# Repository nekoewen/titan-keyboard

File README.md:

# The Titan
The Titan is a QMK-powered keyboard for playing video games, particularly but not exclusively fighting games. The design mixes in bits of the Sega Saturn controller (hence I named it after one of Saturn’s moons) and Hitbox controllers.

## Bill of Materials
- Pro Micro (or a compatible microcontroller, such as an Elite-C, BIT-C, KB2040, etc.) with headers
- 17x 1N4148 through-hole diodes
- 17x key switches (MX or Choc)
- 17x keycaps; 15 should be 1u, and two should be 1.5u
- 9x M2 standoffs
- 18x M2 screws
- 4 or more adhesive rubber feet
- 2-pin reset switch (optional; 3x6x2mm DIP-2P switch, the same kind used on the Corne keyboard)
- EC11 encoder switch with knob (optional)
- WS2182B LED strip and 3 wires (optional)

## Tools
- Soldering iron with solder
- Wire clippers
- Wire stripper (if including an LED strip)
- Screwdriver
- Diode bending tool (optional; I use [this one](https://www.thingiverse.com/thing:4332520))

## Build Guide
1. Begin with the diodes. Bend the leads, insert them through the holes (the cathode is marked with a black line and should go on the square pad, so that the line on the diode matches the one printed on the PCB). Solder each diode, then use clippers to remove the excess leads.
2. Take your Pro Micro and flash the firmware (see below). I recommend doing this before soldering it just in case you got a bad board.
3. Solder the Pro Micro and its header pins to the underside of the board, with the Pro Micro’s components facing the board. You may want to use your clippers to trim off the excess part of the headers. If you’re adding a reset switch, put it into the PCB and solder its pins.
4. If you’re going to use an EC11 encoder, solder it in place now. If you wait until you've soldered the switches, the top plate will being in the way will make it incredibly difficult to get the EC11 in place.
5. From here you should be able to test the keyboard’s functionality. If you plug it in, it should register as a Titan keyboard, and you can use tweezers or a similar metal object to make contact on the switch pads to create the equivalent of keystrokes. If any of the keys don’t work, check to make sure you have the diodes soldered and facing the right direction, and also that the Pro Micro’s pins are all soldered in.
6. Use screws to attach the standoffs to the top plate. It's a bit easier to do this step now.
7. Put the top plate in place, and start pushing switches in place, though the plate and into the PCB so that each switch’s two leads go through the corresponding holes in the PCB. I like to put switches in the corners, solder them in place, and then fill in the rest of the switches. Once you’ve soldered all of the switches, I recommend testing the keyboard again to be sure that you have in fact soldered all of them. Once that’s done you can go ahead and put on the keycaps.
8. If you’re including an LED strip for pretty lights, use 3 wires to solder the pads on the PCB to the corresponding ones on the strip. Be sure the DIn lead is going to LED DAT on the board, as they won’t work if you attach it to DOut on the LED strip. If you plug it into your computer now, it should light up!
9. Flip the keyboard over, put the bottom plate in place (the placement of the screws make it so you need to orient it correctly), and use more screws to secure it in place.
10. Finally, put some adhesive rubber feet on the bottom. You’re done!

## Firmware
You can find a .hex file of the default Titan firmware in this repository. If you don’t have any need to customize the layout, you can just download this and flash it to your Pro Micro.
1. Install [QMK Toolbox](https://github.com/qmk/qmk_toolbox) if you haven’t already.
2. Open titan_default.hex.
3. Click the “Auto-Flash” checkbox.
4. Plug the Pro Micro into your computer.
5. Bridge the GND and RST pins with a metal object (or if it’s already soldered in place, press the reset switch).
6. QMK Toolbox should automatically flash the firmware for you!

If you want to customize the firmware:
1. Copy the “titan” folder from the firmware folder here into the “keyboards” folder of your [QMK installation](https://docs.qmk.fm/#/newbs_getting_started). You can modify the files in this folder as desired.
2. Open a terminal window (for your OS if you’re using macOS or Linux, or [QMK MSYS](https://msys.qmk.fm/) if you’re using Windows).
3. Navigate to the QMK folder (typically `cd qmk_firmware`).
4. Type “`make titan:default`” (or replace “default” with the name of your new keymap) and it should compile.
5. Type “`make titan:default:flash`" (or replace flash with “`dfu`”) to flash it.

If you're using a KB2040 or similar controller, you'll need to use QMK's [Converters](https://github.com/qmk/qmk_firmware/blob/4020674163fc80914059c4c9c3be5c0ae00bd150/docs/feature_converters.md) feature, so for example compiling and flashing for a KB2040 would go as follows:

`qmk flash -c -kb titan -km default -e CONVERT_TO=kb2040`

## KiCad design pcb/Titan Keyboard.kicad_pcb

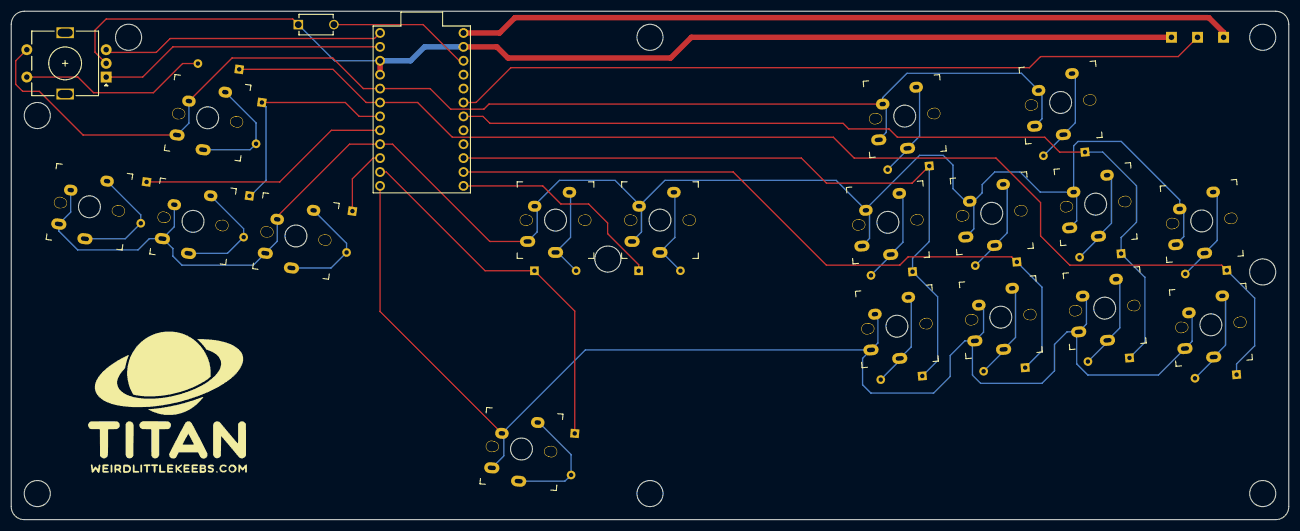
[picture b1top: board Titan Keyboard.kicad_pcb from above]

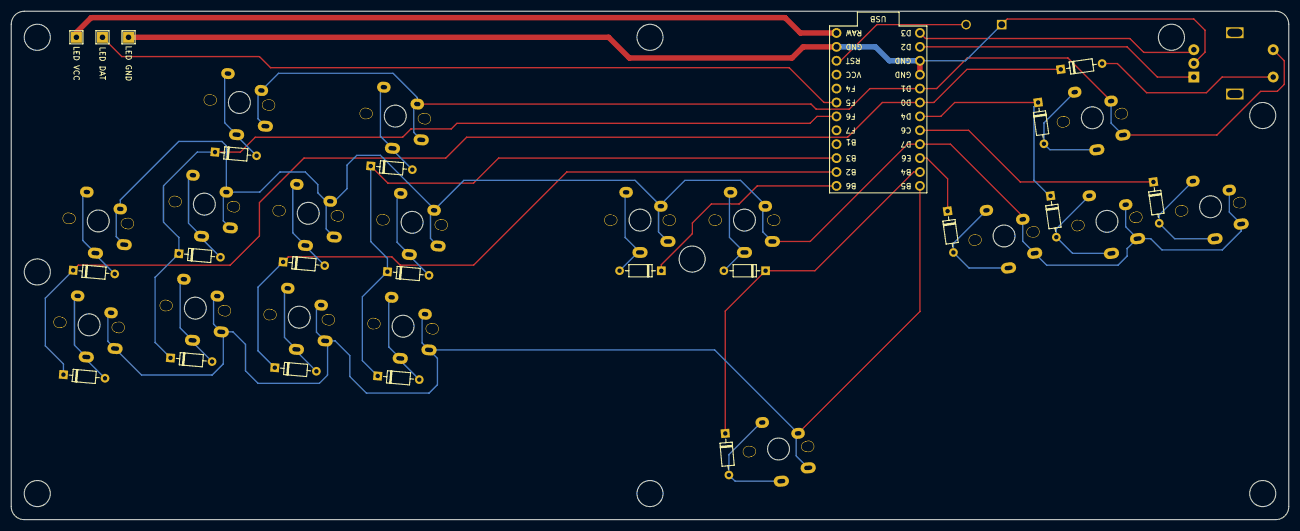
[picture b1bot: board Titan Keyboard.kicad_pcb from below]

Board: 2 copper layers, 233.4 x 92.9 mm, 41 parts (21 on the bottom side), 36 nets.

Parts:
D1, D2, D3, D7, D11, D16, D17, D20, D24, D25, D26, D29, D30, D32, D33, D34, D37, D38: D; D_DO-35_SOD27_P7.62mm_Horizontal
J1: LED VCC; TestPoint_THTPad_2.0x2.0mm_Drill1.0mm
J2: LED DAT; TestPoint_THTPad_2.0x2.0mm_Drill1.0mm
J3: LED GND; TestPoint_THTPad_2.0x2.0mm_Drill1.0mm
SW1: RESET; 1825965-1
SW2: LEFT; CherryMX_Choc_1u
SW3: UP; CherryMX_Choc_1u
SW4: RotaryEncoder_Switch; RotaryEncoder_Alps_EC11E-Switch_Vertical_H20mm
SW8: DWN; CherryMX_Choc_1u
SW12: RIGHT; CherryMX_Choc_1u
SW17: ESC; CherryMX_Choc_1u
SW18: JUMP; CherryMX_Choc_1u
SW21: ENT; CherryMX_Choc_1u
SW25: L1; CherryMX_Choc_1u
SW26: X; CherryMX_Choc_1u
SW27: A; CherryMX_Choc_1u
SW30: Y; CherryMX_Choc_1u
SW31: B; CherryMX_Choc_1u
SW33: R1; CherryMX_Choc_1u
SW34: Z; CherryMX_Choc_1u
SW35: C; CherryMX_Choc_1u
SW38: L2; CherryMX_Choc_1u
SW39: R2; CherryMX_Choc_1u
U1: ProMicro

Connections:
+5V: J1.1, U1.24 (RAW)
COL0: D1.1 (K), U1.8 (C6)
COL1: D2.1 (K), D7.1 (K), U1.7 (D4)
COL2: D11.1 (K), U1.10 (E6)
COL3: D16.1 (K), D17.1 (K), U1.11 (B4)
COL4: D20.1 (K), U1.13 (B6)
COL5: D24.1 (K), D25.1 (K), D26.1 (K), U1.15 (B3)
COL6: D29.1 (K), D30.1 (K), U1.14 (B2)
COL7: D32.1 (K), D33.1 (K), D34.1 (K), U1.18 (F6)
COL8: D3.1 (K), D37.1 (K), D38.1 (K), U1.6 (SCL)
ENC_A: SW4.A, U1.2 (RX)
ENC_B: SW4.B, U1.1 (TX)
GND: J3.1, SW1.1, SW4.C, U1.3 (GND), U1.4 (GND), U1.23 (GND)
LED_DAT: J2.1, U1.19 (F5)
unnamed: D1.2 (A), SW2.2
unnamed: D2.2 (A), SW3.2
unnamed: D3.2 (A), SW4.S2
unnamed: D7.2 (A), SW8.2
unnamed: D11.2 (A), SW12.2
unnamed: D16.2 (A), SW17.2
unnamed: D17.2 (A), SW18.2
unnamed: D20.2 (A), SW21.2
unnamed: D24.2 (A), SW25.2
unnamed: D25.2 (A), SW26.2
unnamed: D26.2 (A), SW27.2
unnamed: D29.2 (A), SW30.2
unnamed: D30.2 (A), SW31.2
unnamed: D32.2 (A), SW33.2
unnamed: D33.2 (A), SW34.2
unnamed: D34.2 (A), SW35.2
unnamed: D37.2 (A), SW38.2
unnamed: D38.2 (A), SW39.2
RESET: SW1.2, U1.22 (RST)
ROW0: SW3.1, SW4.S1, SW25.1, SW33.1, U1.5 (SDA)
ROW1: SW2.1, SW8.1, SW12.1, SW17.1, SW21.1, SW26.1, SW30.1, SW34.1, SW38.1, U1.9 (D7)
ROW2: SW18.1, SW27.1, SW31.1, SW35.1, SW39.1, U1.12 (B5)

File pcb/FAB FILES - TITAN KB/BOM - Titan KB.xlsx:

Ref | Qnty | Value | Footprint | MPN | MANUFACTURER
D1, D2, D3, D7, D11, D16, D17, D20, D24, D25, D26, D29, D30, D32, D33, D34, D37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 | 18 | D | Diode_THT:D_DO-35_SOD27_P7.62mm_Horizontal | 1N4148 | onsemi
J1, | 1 | LED VCC | TestPoint:TestPoint_THTPad_2.0x2.0mm_Drill1.0mm | DNP | DNP
J2, | 1 | LED DAT | TestPoint:TestPoint_THTPad_2.0x2.0mm_Drill1.0mm | DNP | DNP
J3, | 1 | LED GND | TestPoint:TestPoint_THTPad_2.0x2.0mm_Drill1.0mm | DNP | DNP
SW1, | 1 | RESET | FOOTPRINTS:1825965-1 | 1825965-1 | TE Connectivity
SW2, | 1 | LEFT | FOOTPRINTS:CherryMX_Choc_1u
SW3, | 1 | UP | FOOTPRINTS:CherryMX_Choc_1u
SW4, | 1 | RotaryEncoder_Switch | Rotary_Encoder:RotaryEncoder_Alps_EC11E-Switch_Vertical_H20mm | EC11E | ALPSALPINE
SW8, | 1 | DWN | FOOTPRINTS:CherryMX_Choc_1u
SW12, | 1 | RIGHT | FOOTPRINTS:CherryMX_Choc_1u
SW17, | 1 | ESC | FOOTPRINTS:CherryMX_Choc_1u
SW18, | 1 | JUMP | FOOTPRINTS:CherryMX_Choc_1u
SW21, | 1 | ENT | FOOTPRINTS:CherryMX_Choc_1u
SW25, | 1 | L1 | FOOTPRINTS:CherryMX_Choc_1u
SW26, | 1 | X | FOOTPRINTS:CherryMX_Choc_1u
SW27, | 1 | A | FOOTPRINTS:CherryMX_Choc_1u
SW30, | 1 | Y | FOOTPRINTS:CherryMX_Choc_1u
SW31, | 1 | B | FOOTPRINTS:CherryMX_Choc_1u
SW33, | 1 | R1 | FOOTPRINTS:CherryMX_Choc_1u
SW34, | 1 | Z | FOOTPRINTS:CherryMX_Choc_1u
SW35, | 1 | C | FOOTPRINTS:CherryMX_Choc_1u
SW38, | 1 | L2 | FOOTPRINTS:CherryMX_Choc_1u
SW39, | 1 | R2 | FOOTPRINTS:CherryMX_Choc_1u
U1, | 1 | ProMicro | FOOTPRINTS:ProMicro | Pro Micro | Sparkfun
